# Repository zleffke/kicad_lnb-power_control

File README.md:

# kicad_lnb-power_control
Dual X-Band LNB Power Control for VTGS SX-Band System

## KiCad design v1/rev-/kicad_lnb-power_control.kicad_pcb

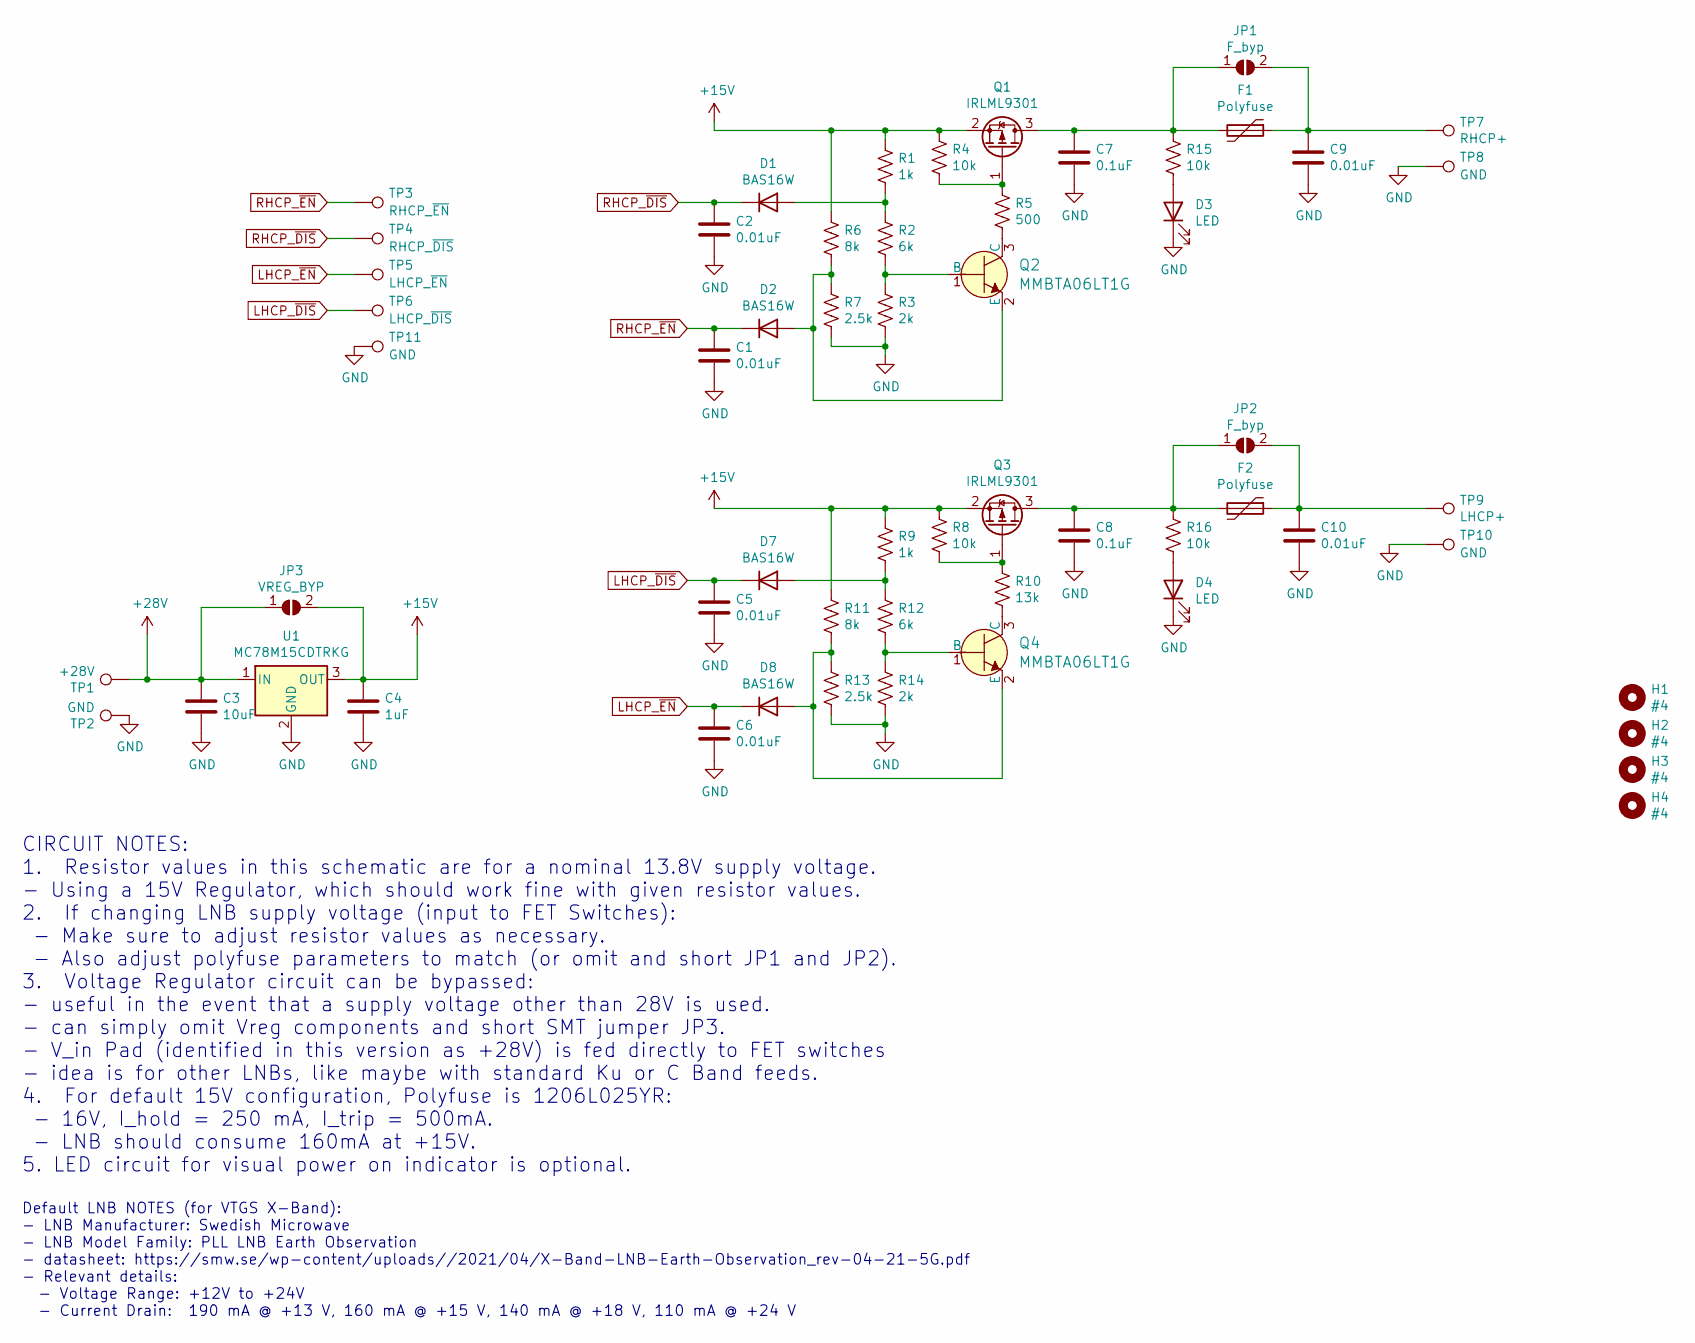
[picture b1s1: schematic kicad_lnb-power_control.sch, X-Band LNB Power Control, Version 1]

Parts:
C1, C2, C5, C6, C9, C10: 0.01uF; 0805
C3: 10uF; 0805
C4: 1uF; 0805
C7, C8: 0.1uF; 0805
D1, D2, D7, D8: BAS16W; SOT-23-3
D3, D4: LED; LED_0805_2012Metric
F1, F2: Polyfuse; 1206
H1, H2, H3, H4: #4; MountingHole_3.2mm_M3
JP1, JP2: F_byp; SolderJumper-2_P1.3mm_Open_RoundedPad1.0x1.5mm
JP3: VREG_BYP; SolderJumper-2_P1.3mm_Open_RoundedPad1.0x1.5mm
Q1, Q3: IRLML9301; SOT-23-3
Q2, Q4: MMBTA06LT1G; SOT-23-3; MPN MMBTA06LT1G; Digi-Key_PN MMBTA06LT1GOSCT-ND
R1, R9: 1k; 0805
R2, R12: 6k; 0805
R3, R14: 2k; 0805
R4, R8, R15, R16: 10k; 0805
R5: 500; 0805
R6, R11: 8k; 0805
R7, R13: 2.5k; 0805
R10: 13k; 0805
TP1: +28V; TestPoint_Pad_2.5x2.5mm
TP2: GND; TestPoint_Pad_2.5x2.5mm
TP3: RHCP_~EN; TestPoint_Pad_2.0x2.0mm
TP4: RHCP_~DIS; TestPoint_Pad_2.0x2.0mm
TP5: LHCP_~EN; TestPoint_Pad_2.0x2.0mm
TP6: LHCP_~DIS; TestPoint_Pad_2.0x2.0mm
TP7: RHCP+; TestPoint_Pad_2.0x2.0mm
TP8, TP10, TP11: GND; TestPoint_Pad_2.0x2.0mm
TP9: LHCP+; TestPoint_Pad_2.0x2.0mm
U1: MC78M15CDTRKG; TO-252-2

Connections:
+15V: C4.1, JP3.2 (B), Q1.2 (S), Q3.2 (S), R1.1, R4.1, R6.1, R8.1, R9.1, R11.1, U1.3 (OUT)
+28V: C3.1, JP3.1 (A), TP1.1, U1.1 (IN)
GND: C1.2, C2.2, C3.2, C4.2, C5.2, C6.2, C7.2, C8.2, C9.2, C10.2, D3.1 (K), D4.1 (K), R3.2, R7.2, R13.2, R14.2, TP2.1, TP8.1, TP10.1, TP11.1, U1.2 (GND)
LHCP_~DIS: C5.1, D7.3 (K), TP6.1
LHCP_~EN: C6.1, D8.3 (K), TP5.1
unnamed: C7.1, F1.2, JP1.1 (A), Q1.3 (D), R15.1
unnamed: C8.1, F2.2, JP2.1 (A), Q3.3 (D), R16.1
unnamed: C9.1, F1.1, JP1.2 (B), TP7.1
unnamed: C10.1, F2.1, JP2.2 (B), TP9.1
unnamed: D1.1 (A), R1.2, R2.1
unnamed: D2.1 (A), Q2.2 (E), R6.2, R7.1
unnamed: D3.2 (A), R15.2
unnamed: D4.2 (A), R16.2
unnamed: D7.1 (A), R9.2, R12.1
unnamed: D8.1 (A), Q4.2 (E), R11.2, R13.1
unnamed: Q1.1 (G), R4.2, R5.1
unnamed: Q2.1 (B), R2.2, R3.1
unnamed: Q2.3 (C), R5.2
unnamed: Q3.1 (G), R8.2, R10.1
unnamed: Q4.1 (B), R12.2, R14.1
unnamed: Q4.3 (C), R10.2
RHCP_~DIS: C2.1, D1.3 (K), TP4.1
RHCP_~EN: C1.1, D2.3 (K), TP3.1

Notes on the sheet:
Default LNB NOTES (for VTGS X-Band): - LNB Manufacturer: Swedish Microwave - LNB Model Family: PLL LNB Earth Observation - datasheet: https://smw.se/wp-content/uploads//2021/04/X-Band-LNB-Earth-Observation_rev-04-21-5G.pdf - Relevant details: - Voltage Range: +12V to +24V - Current Drain: 190 mA @ 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
CIRCUIT NOTES: 1. Resistor values in this schematic are for a nominal 13.8V supply voltage. - Using a 15V Regulator, which should work fine with given resistor values. 2. If changing LNB supply voltage (input to FET Switches): - Make sure to adjust resistor values as necessary. - Also adjust polyfu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

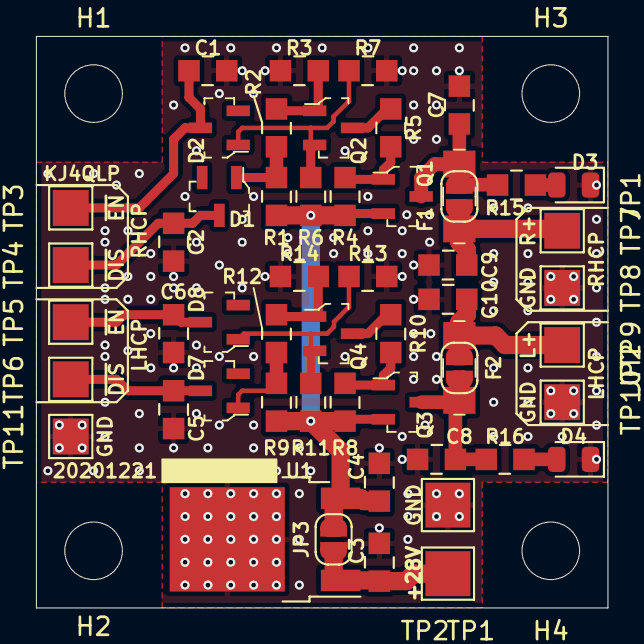
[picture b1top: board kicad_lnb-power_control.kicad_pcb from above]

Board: 2 copper layers, 31.8 x 31.8 mm, 57 parts (0 on the bottom side), 23 nets.

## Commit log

2022-01-22 initial commit. Compleded v1, rev-. This commit submitted to osh park 20220122.

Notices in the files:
v1/rev-/kicad_lnb-power_control.sch:
creativecommons.org/licenses/by/4.0
License: CC BY 4.0
